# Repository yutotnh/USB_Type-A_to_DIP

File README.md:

# USB_Type-A_to_DIP
USB Type-A ををDIPで使えるようにする基板

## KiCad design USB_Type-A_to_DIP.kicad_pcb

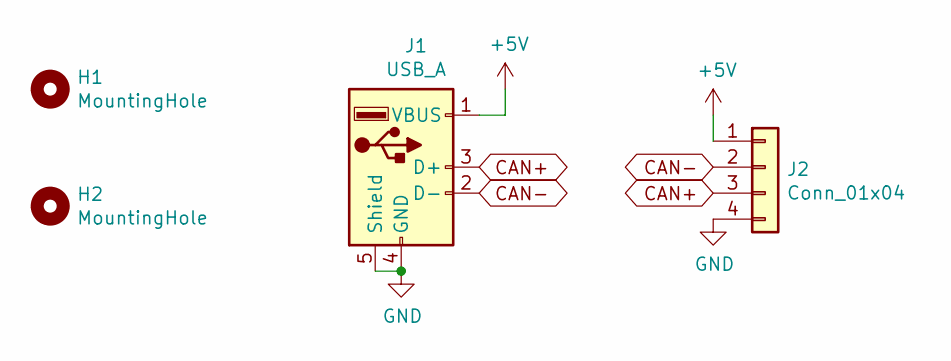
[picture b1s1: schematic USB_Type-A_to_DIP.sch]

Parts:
H1, H2: MountingHole; MountingHole_3.2mm_M3
J1: USB_A; USB_A_Molex_67643_Horizontal
J2: Conn_01x04; PinHeader_1x04_P2.54mm_Vertical

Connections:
+5V: J1.1 (VBUS), J2.1
CAN+: J1.3 (D+), J2.3
CAN-: J1.2 (D-), J2.2
GND: J1.4 (GND), J1.5 (Shield), J2.4

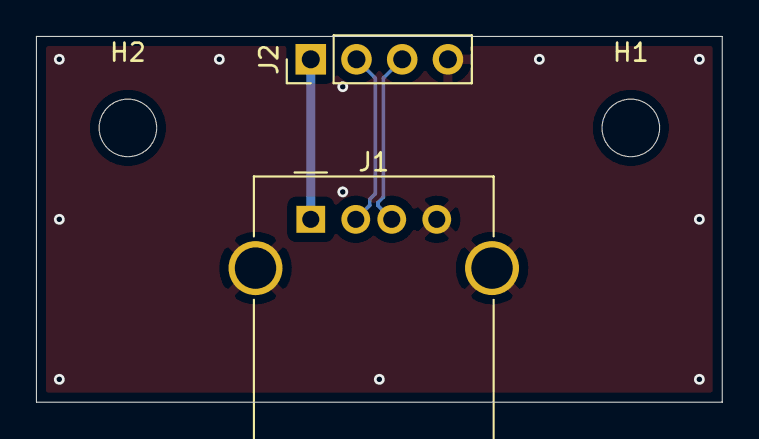
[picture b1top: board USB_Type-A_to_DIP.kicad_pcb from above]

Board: 2 copper layers, 38.1 x 20.3 mm, 4 parts (0 on the bottom side), 4 nets.
